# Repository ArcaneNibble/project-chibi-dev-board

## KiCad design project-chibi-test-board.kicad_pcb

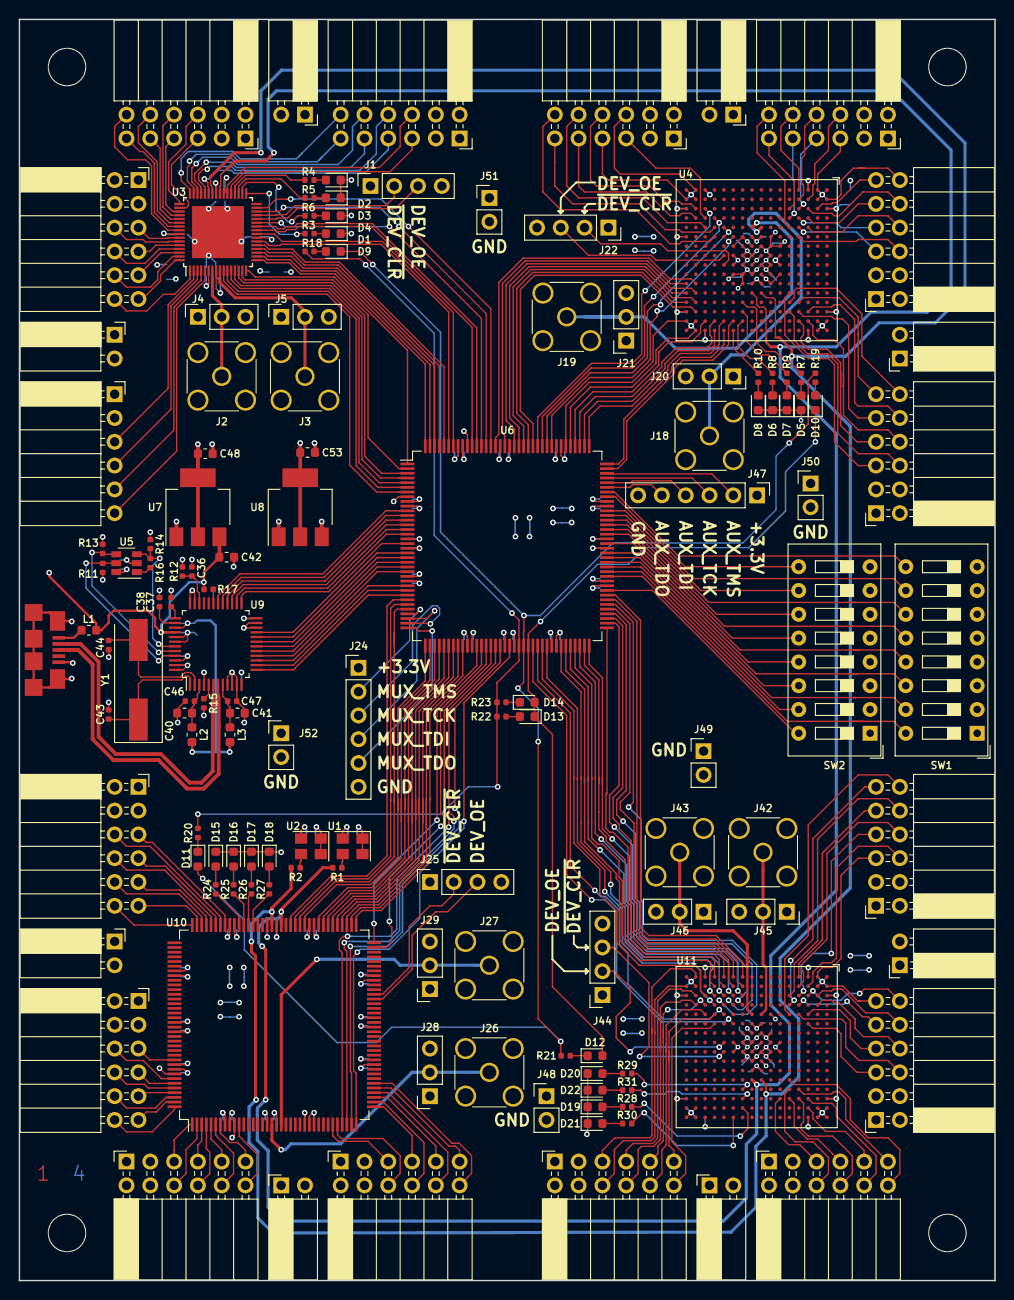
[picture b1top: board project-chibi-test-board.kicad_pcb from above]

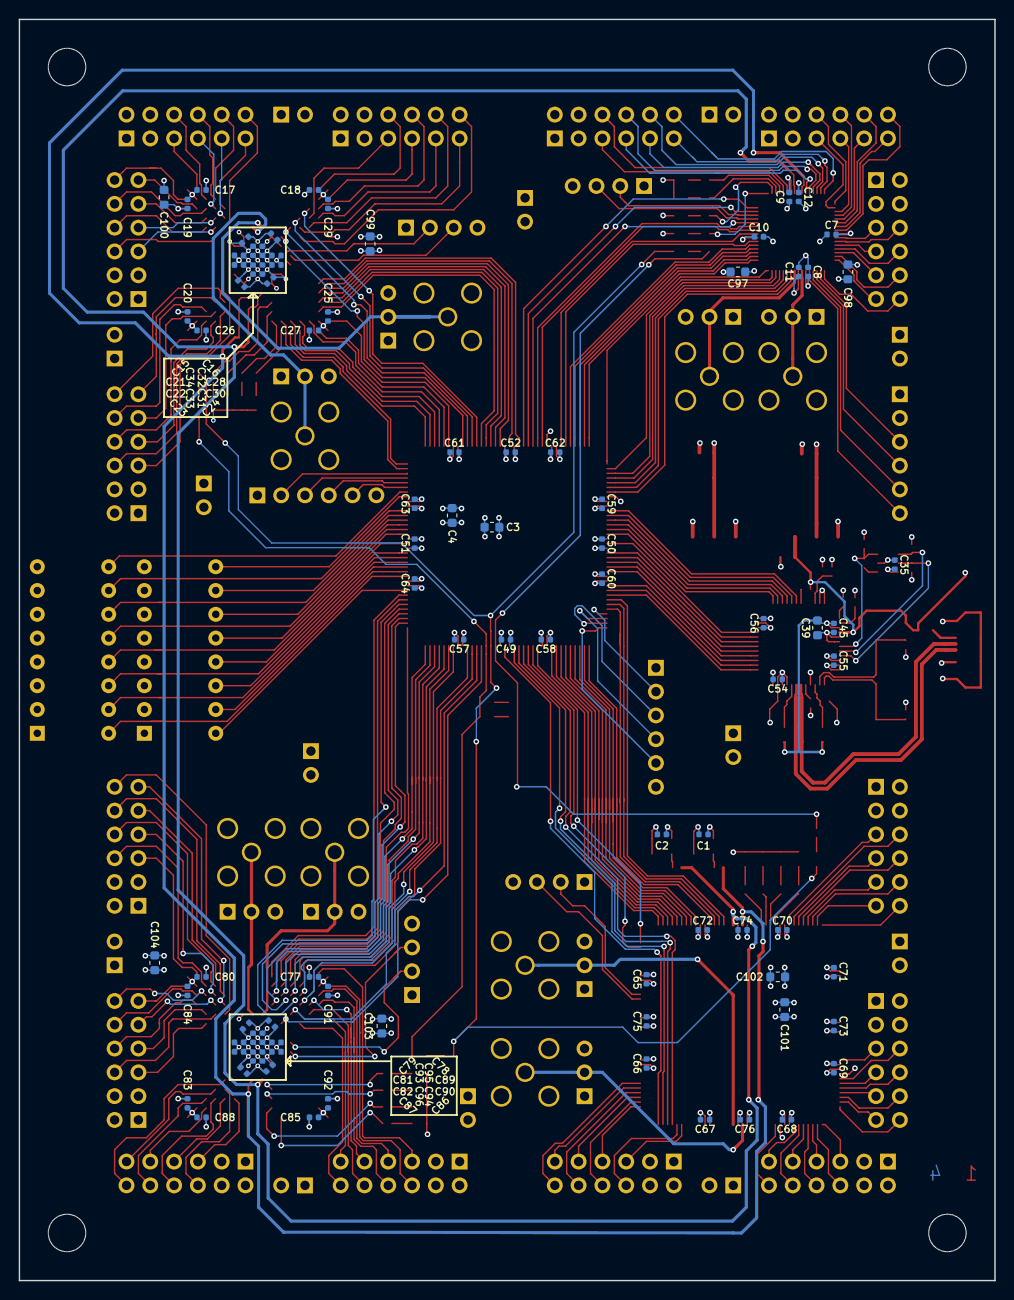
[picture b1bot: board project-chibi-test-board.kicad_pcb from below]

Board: 4 copper layers, 104.1 x 134.6 mm, 226 parts (88 on the bottom side), 321 nets.

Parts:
C1, C2, C7, C8, C9, C10, C11, C12, C15, C16, C17, C18, C19, C20, C21, C22, C23, C24, C25, C26, C27, C28, C29, C30, C31, C32, C33, C34, C35, C37, C38, C45, C46, C47, C49, C50, C51, C52, C54, C55, C56, C57, C58, C59, C60, C61, C62, C63, C64, C65, C66, C67, C68, C69, C70, C71, C72, C73, C74, C75, C76, C77, C78, C79, C80, C81, C82, C83, C84, C85, C86, C87, C88, C89, C90, C91, C92, C93, C94, C95, C96: 0.1 uF; C_0402_1005Metric
C3, C4, C39, C40, C41, C42, C48, C53, C97, C98, C99, C100, C101, C102, C103, C104: 4.7 uF; C_0603_1608Metric
C36: 10 nF; C_0402_1005Metric
C43, C44: 20 pF; C_0402_1005Metric
D1, D2, D3, D4, D5, D6, D7, D8, D15, D16, D17, D18, D19, D20, D21, D22: GREEN; LED_0603_1608Metric
D9, D10, D11, D12: RED; LED_0603_1608Metric
D13, D14: YELLOW; LED_0603_1608Metric
J1, J22, J25, J44: Conn_01x04; PinSocket_1x04_P2.54mm_Vertical
J2, J3, J18, J19, J26, J27, J42, J43: Conn_Coaxial; SMA_Amphenol_132134_Vertical
J4, J5, J20, J21, J28, J29, J45, J46: Conn_01x03; PinSocket_1x03_P2.54mm_Vertical
J6, J7, J8, J12, J13, J14, J15, J32, J33, J34, J35, J36, J37, J38, J39: Conn_02x06_Top_Bottom; PinSocket_2x06_P2.54mm_Horizontal
J9: Conn_01x06; PinSocket_1x06_P2.54mm_Horizontal
J10, J11, J16, J17, J30, J31, J40, J41: Conn_01x02; PinSocket_1x02_P2.54mm_Horizontal
J23: USB_B_Micro; USB-MICRO-AB
J24, J47: Conn_01x06; PinHeader_1x06_P2.54mm_Vertical
J48, J49, J50, J51, J52: Conn_01x02; PinHeader_1x02_P2.54mm_Vertical
L1, L2, L3: MPZ1608S601ATA00; L_0603_1608Metric
MK1, MK2, MK3, MK4: Mounting_Hole; MountingHole_4mm
R1, R2: 49.9; R_0402_1005Metric
R3, R4, R5, R6, R7, R8, R9, R10, R18, R19, R20, R21, R22, R23, R24, R25, R26, R27, R28, R29, R30, R31: 330; R_0402_1005Metric
R11, R12, R13, R14: 10k; R_0402_1005Metric
R15: 12k 1%; R_0402_1005Metric
R16: 2k; R_0402_1005Metric
R17: 39k; R_0402_1005Metric
SW1, SW2: SW_DIP_x08; SW_DIP_SPSTx08_Slide_9.78x22.5mm_W7.62mm_P2.54mm
U1: 40 MHz; Oscillator_SMD_Abracon_ASE-4Pin_3.2x2.5mm
U2: 2.048 MHz; Oscillator_SMD_Abracon_ASE-4Pin_3.2x2.5mm
U3: 5M40ZE64C5N; TQFP-64-1EP_7x7mm_P0.4mm_EP4.5x4.5mm
U4: 5M2210ZF256C5N; BGA-256_17.0x17.0mm_Layout16x16_P1.0mm_Ball0.5mm_Pad0.4mm_N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
U5: 93LC56BT-OT; SOT-23-6
U6, U10: 5M240ZT144C5N; TQFP-144_20x20mm_P0.5mm
U7: LM1117-3.3; SOT-223-3_TabPin2
U8: LM1117-1.8; SOT-223-3_TabPin2
U9: FT232H; LQFP-48_7x7mm_P0.5mm
U11: 5M1270ZF256C5N; BGA-256_17.0x17.0mm_Layout16x16_P1.0mm_Ball0.5mm_Pad0.4mm_N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
Y1: 12 MHz; Crystal_SMD_HC49-SD

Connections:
+1V8: C3.1, C11.1, C12.1, C31.1, C32.1, C33.1, C34.1, C49.1, C50.1, C51.1, C52.1, C53.1, C73.1, C74.1, C75.1, C76.1, C93.1, C94.1, C95.1, C96.1, C97.1, C99.1, C101.1, C103.1, U3.8, U3.41, U4.F10, U4.G11, U4.H8, U4.H10, U4.J7, U4.J9, U4.K6, U4.L7, U6.19, U6.56, U6.90, U6.126, U8.2, U10.19, U10.56, U10.90, U10.126, U11.H8, U11.H10, U11.J7, U11.J9
+3V3: C1.1, C2.1, C4.1, C7.1, C8.1, C9.1, C10.1, C15.1, C16.1, C17.1, C18.1, C19.1, C20.1, C21.1, C22.1, C23.1, C24.1, C25.1, C26.1, C27.1, C28.1, C29.1, C30.1, C35.1, C48.1, C54.1, C55.1, C56.1, C57.1, C58.1, C59.1, C60.1, C61.1, C62.1, C63.1, C64.1, C65.1, C66.1, C67.1, C68.1, C69.1, C70.1, C71.1, C72.1, C77.1, C78.1, C79.1, C80.1, C81.1, C82.1, C83.1, C84.1, C85.1, C86.1, C87.1, C88.1, C89.1, C90.1, C91.1, C92.1, C98.1, C100.1, C102.1, C104.1, J1.1, J6.1, J6.2, J7.1, J7.2, J8.1, J8.2, J9.1, J12.1, J12.2, J13.1, J13.2, J14.1, J14.2, J15.1, J15.2, J22.1, J24.1, J25.1, J32.1, J32.2, J33.1, J33.2, J34.1, J34.2, J35.1, J35.2, J36.1, J36.2, J37.1, J37.2, J38.1, J38.2, J39.1, J39.2, J44.1, J47.1, R11.1, R12.1, R13.1, R14.1, U1.1, U1.4, U2.1, U2.4, U3.6, U3.23, U3.39, U3.57, U4.A3, U4.A14, U4.C1, U4.C16, U4.F8, U4.F9, U4.H6, U4.H11, U4.J6, U4.J11, U4.L8, U4.L9, U4.P1, U4.P16, U4.T3, U4.T14, U5.6, U6.9, U6.25, U6.46, U6.64, U6.82, U6.100, U6.116, U6.136, U7.2, U8.3, U9.12, U9.24, U9.46, U10.9, U10.25, U10.46, U10.64, U10.82, U10.100, U10.116, U10.136, U11.A3, U11.A14, U11.C1, U11.C16, U11.F8, U11.F9, U11.H6, U11.H11, U11.J6, U11.J11, U11.L8, U11.L9, U11.P1, U11.P16, U11.T3, U11.T14
+5V: C42.1, J10.2, J11.2, J16.2, J17.2, J30.2, J31.2, J40.2, J41.2, L1.1, R17.1, U7.3, U9.40
/CLK_2.048MHZ: R2.1, U3.42, U4.H12, U10.91, U11.H12
/CLK_40MHZ: R1.1, U3.40, U4.J12, U10.89, U11.J12
/jtag-iface/ACBUS0: U6.18, U9.21
/jtag-iface/ACBUS1: U6.16, U9.25
/jtag-iface/ACBUS2: U6.15, U9.26
/jtag-iface/ACBUS3: U6.14, U9.27
/jtag-iface/ACBUS4: U6.13, U9.28
/jtag-iface/ACBUS5: U6.12, U9.29
/jtag-iface/ACBUS6: U6.11, U9.30
/jtag-iface/ADBUS0: U6.29, U9.13
/jtag-iface/ADBUS1: U6.28, U9.14
/jtag-iface/ADBUS2: U6.27, U9.15
/jtag-iface/ADBUS3: U6.24, U9.16
/jtag-iface/ADBUS4: U6.23, U9.17
/jtag-iface/ADBUS5: U6.22, U9.18
/jtag-iface/ADBUS6: U6.21, U9.19
/jtag-iface/ADBUS7: U6.20, U9.20
/jtag-iface/AUXJTAG_TCK: J47.3, U6.105
/jtag-iface/AUXJTAG_TDI: J47.4, U6.104
/jtag-iface/AUXJTAG_TDO: J47.5, U6.103
/jtag-iface/AUXJTAG_TMS: J47.2, U6.106
/jtag-iface/FTDI_VCCD: C39.1, C45.1, L2.2, L3.2, U9.39
/jtag-iface/FTDI_VPHY: C40.1, C46.1, L2.1, U9.3
/jtag-iface/FTDI_VPLL: C41.1, C47.1, L3.1, U9.8
/jtag-iface/MUX_TCK: J24.3, U6.35
/jtag-iface/MUX_TDI: J24.4, U6.34
/jtag-iface/MUX_TDO: J24.5, U6.36
/jtag-iface/MUX_TMS: J24.2, U6.33
/jtag-iface/USB_N: J23.2, U9.6
/jtag-iface/USB_P: J23.3, U9.7
/tgt-4x6/ACBUS0: U3.25, U6.134
/tgt-4x6/ACBUS1: U3.24, U6.138
/tgt-4x6/ACBUS2: U3.22, U6.139
/tgt-4x6/ACBUS3: U3.27, U6.132
/tgt-4x6/ACBUS4: U3.26, U6.133
/tgt-4x6/ACBUS5: U3.31, U6.130
/tgt-4x6/ACBUS6: U3.30, U6.131
/tgt-4x6/ADBUS0: U3.10, U6.7
/tgt-4x6/ADBUS1: U3.11, U6.6
/tgt-4x6/ADBUS2: U3.12, U6.5
/tgt-4x6/ADBUS3: U3.13, U6.4
/tgt-4x6/ADBUS4: U3.21, U6.140
/tgt-4x6/ADBUS5: U3.20, U6.141
/tgt-4x6/ADBUS6: U3.19, U6.142
/tgt-4x6/ADBUS7: U3.18, U6.143
/tgt-4x6/CLKIN0: J2.1, J4.2, U3.7
/tgt-4x6/CLKIN1: J3.1, J5.2, U3.9
/tgt-4x6/DEV_OE: J1.3, U3.28
/tgt-4x6/EXPAND0_0: J6.12, U3.1
/tgt-4x6/EXPAND0_1: J6.10, U3.63
/tgt-4x6/EXPAND0_2: J6.8, U3.61
/tgt-4x6/EXPAND0_3: J6.6, U3.59
/tgt-4x6/EXPAND0_4: J6.11, U3.64
/tgt-4x6/EXPAND0_5: J6.9, U3.62
/tgt-4x6/EXPAND0_6: J6.7, U3.60
/tgt-4x6/EXPAND0_7: J6.5, U3.58
/tgt-4x6/EXPAND1_0: J7.12, U3.56
/tgt-4x6/EXPAND1_1: J7.10, U3.54
/tgt-4x6/EXPAND1_2: J7.8, U3.52
/tgt-4x6/EXPAND1_3: J7.6, U3.49
/tgt-4x6/EXPAND1_4: J7.11, U3.55
/tgt-4x6/EXPAND1_5: J7.9, U3.53
/tgt-4x6/EXPAND1_6: J7.7, U3.51
/tgt-4x6/EXPAND1_7: J7.5, U3.50
/tgt-4x6/EXPAND2_0: J8.12, U3.48
/tgt-4x6/EXPAND2_1: J8.10, U3.46
/tgt-4x6/EXPAND2_2: J8.8, U3.44
/tgt-4x6/EXPAND2_3: J8.6, U3.38
/tgt-4x6/EXPAND2_4: J8.11, U3.47
/tgt-4x6/EXPAND2_5: J8.9, U3.45
/tgt-4x6/EXPAND2_6: J8.7, U3.43
/tgt-4x6/EXPAND2_7: J8.5, U3.37
/tgt-4x6/EXPAND3_0: J9.6, U3.5
/tgt-4x6/EXPAND3_1: J9.5, U3.4
/tgt-4x6/EXPAND3_2: J9.4, U3.3
/tgt-4x6/EXPAND3_3: J9.3, U3.2
/tgt-4x6/JTAG_TCK: U3.16, U6.1
/tgt-4x6/JTAG_TDI: U3.15, U6.2
/tgt-4x6/JTAG_TDO: U3.17, U6.144
/tgt-4x6/JTAG_TMS: U3.14, U6.3
/tgt-4x6/~DEV_CLR: J1.2, U3.29
/tgt-7x12/ACBUS0: U6.42, U10.77
/tgt-7x12/ACBUS1: U6.43, U10.76
/tgt-7x12/ACBUS2: U6.44, U10.75
/tgt-7x12/ACBUS3: U6.45, U10.74
/tgt-7x12/ACBUS4: U6.48, U10.73
/tgt-7x12/ACBUS5: U6.49, U10.72
/tgt-7x12/ACBUS6: U6.50, U10.71
/tgt-7x12/ADBUS0: U6.30, U10.87
/tgt-7x12/ADBUS1: U6.31, U10.86
/tgt-7x12/ADBUS2: U6.32, U10.85
/tgt-7x12/ADBUS3: U6.37, U10.84
/tgt-7x12/ADBUS4: U6.38, U10.81
/tgt-7x12/ADBUS5: U6.39, U10.80
/tgt-7x12/ADBUS6: U6.40, U10.79
/tgt-7x12/ADBUS7: U6.41, U10.78
/tgt-7x12/CLKIN0: J26.1, J28.2, U10.18
/tgt-7x12/CLKIN1: J27.1, J29.2, U10.20
/tgt-7x12/DEV_OE: J25.3, U10.60
/tgt-7x12/EXPAND0_0: J32.12, U10.11
/tgt-7x12/EXPAND0_1: J32.10, U10.6
/tgt-7x12/EXPAND0_2: J32.8, U10.4
/tgt-7x12/EXPAND0_3: J32.6, U10.2
/tgt-7x12/EXPAND0_4: J32.11, U10.7
/tgt-7x12/EXPAND0_5: J32.9, U10.5
/tgt-7x12/EXPAND0_6: J32.7, U10.3
/tgt-7x12/EXPAND0_7: J32.5, U10.1
/tgt-7x12/EXPAND1_0: J33.12, U10.42
/tgt-7x12/EXPAND1_1: J33.10, U10.40
/tgt-7x12/EXPAND1_2: J33.8, U10.38
/tgt-7x12/EXPAND1_3: J33.6, U10.32
/tgt-7x12/EXPAND1_4: J33.11, U10.41
/tgt-7x12/EXPAND1_5: J33.9, U10.39
/tgt-7x12/EXPAND1_6: J33.7, U10.37
/tgt-7x12/EXPAND1_7: J33.5, U10.31
/tgt-7x12/EXPAND2_0: J34.12, U10.108
/tgt-7x12/EXPAND2_1: J34.10, U10.106
/tgt-7x12/EXPAND2_2: J34.8, U10.104
/tgt-7x12/EXPAND2_3: J34.6, U10.102
/tgt-7x12/EXPAND2_4: J34.11, U10.107
/tgt-7x12/EXPAND2_5: J34.9, U10.105
/tgt-7x12/EXPAND2_6: J34.7, U10.103
/tgt-7x12/EXPAND2_7: J34.5, U10.101
/tgt-7x12/EXPAND3_0: J35.12, U10.144
/tgt-7x12/EXPAND3_1: J35.10, U10.142
/tgt-7x12/EXPAND3_2: J35.8, U10.140
/tgt-7x12/EXPAND3_3: J35.6, U10.138
/tgt-7x12/EXPAND3_4: J35.11, U10.143
/tgt-7x12/EXPAND3_5: J35.9, U10.141
/tgt-7x12/EXPAND3_6: J35.7, U10.139
/tgt-7x12/EXPAND3_7: J35.5, U10.134
/tgt-7x12/JTAG_TCK: U6.53, U10.35
/tgt-7x12/JTAG_TDI: U6.52, U10.34
/tgt-7x12/JTAG_TDO: U6.55, U10.36
/tgt-7x12/JTAG_TMS: U6.51, U10.33
/tgt-7x12/~DEV_CLR: J25.2, U10.61
/tgt-10x16/ACBUS0: U6.72, U11.K3
/tgt-10x16/ACBUS1: U6.70, U11.L3
/tgt-10x16/ACBUS2: U6.68, U11.M3
/tgt-10x16/ACBUS3: U6.66, U11.N3
/tgt-10x16/ACBUS4: U6.74, U11.K4
/tgt-10x16/ACBUS5: U6.76, U11.L4
/tgt-10x16/ACBUS6: U6.78, U11.M4
/tgt-10x16/ADBUS0: U6.80, U11.K1
/tgt-10x16/ADBUS1: U6.79, U11.K2
/tgt-10x16/ADBUS2: U6.77, U11.L1
/tgt-10x16/ADBUS3: U6.75, U11.L2
/tgt-10x16/ADBUS4: U6.73, U11.M1
/tgt-10x16/ADBUS5: U6.71, U11.M2
/tgt-10x16/ADBUS6: U6.69, U11.N1
/tgt-10x16/ADBUS7: U6.67, U11.N2
/tgt-10x16/CLK0: J42.1, J45.2, U11.H5
/tgt-10x16/CLK1: J43.1, J46.2, U11.J5
/tgt-10x16/DEV_OE: J44.2, U11.M8
/tgt-10x16/EXPAND0_0: J36.12, U11.C3
/tgt-10x16/EXPAND0_1: J36.10, U11.B3
/tgt-10x16/EXPAND0_2: J36.8, U11.B4
/tgt-10x16/EXPAND0_3: J36.6, U11.D5
/tgt-10x16/EXPAND0_4: J36.11, U11.A2
/tgt-10x16/EXPAND0_5: J36.9, U11.D4
/tgt-10x16/EXPAND0_6: J36.7, U11.C5
/tgt-10x16/EXPAND0_7: J36.5, U11.C6
/tgt-10x16/EXPAND1_0: J37.12, U11.E5
/tgt-10x16/EXPAND1_1: J37.10, U11.E3
/tgt-10x16/EXPAND1_2: J37.8, U11.D2
/tgt-10x16/EXPAND1_3: J37.6, U11.C2
/tgt-10x16/EXPAND1_4: J37.11, U11.E4
/tgt-10x16/EXPAND1_5: J37.9, U11.D1
/tgt-10x16/EXPAND1_6: J37.7, U11.D3
/tgt-10x16/EXPAND1_7: J37.5, U11.B1
/tgt-10x16/EXPAND2_0: J38.12, U11.E12
/tgt-10x16/EXPAND2_1: J38.10, U11.C14
/tgt-10x16/EXPAND2_2: J38.8, U11.D14
/tgt-10x16/EXPAND2_3: J38.6, U11.E13
/tgt-10x16/EXPAND2_4: J38.11, U11.D13
/tgt-10x16/EXPAND2_5: J38.9, U11.C15
/tgt-10x16/EXPAND2_6: J38.7, U11.E14
/tgt-10x16/EXPAND2_7: J38.5, U11.F14
/tgt-10x16/EXPAND3_0: J39.12, U11.N6
/tgt-10x16/EXPAND3_1: J39.10, U11.P5
/tgt-10x16/EXPAND3_2: J39.8, U11.R4
/tgt-10x16/EXPAND3_3: J39.6, U11.T2
/tgt-10x16/EXPAND3_4: J39.11, U11.N5
/tgt-10x16/EXPAND3_5: J39.9, U11.P4
/tgt-10x16/EXPAND3_6: J39.7, U11.R3
/tgt-10x16/EXPAND3_7: J39.5, U11.R1
/tgt-10x16/JTAG_TCK: U6.62, U11.P3
/tgt-10x16/JTAG_TDI: U6.60, U11.L6
/tgt-10x16/JTAG_TDO: U6.61, U11.M5
/tgt-10x16/JTAG_TMS: U6.63, U11.N4
/tgt-10x16/~DEV_CLR: J44.3, U11.M9
/tgt-13x20/ACBUS0: U4.R14, U6.121
/tgt-13x20/ACBUS1: U4.T13, U6.122
/tgt-13x20/ACBUS2: U4.R13, U6.123
/tgt-13x20/ACBUS3: U4.T12, U6.124
/tgt-13x20/ACBUS4: U4.R12, U6.125
/tgt-13x20/ACBUS5: U4.T11, U6.127
/tgt-13x20/ACBUS6: U4.R11, U6.129
/tgt-13x20/ADBUS0: U4.L15, U6.107
/tgt-13x20/ADBUS1: U4.M16, U6.108
/tgt-13x20/ADBUS2: U4.M15, U6.109
/tgt-13x20/ADBUS3: U4.N16, U6.110
/tgt-13x20/ADBUS4: U4.N15, U6.111
/tgt-13x20/ADBUS5: U4.P15, U6.112
/tgt-13x20/ADBUS6: U4.T15, U6.114
/tgt-13x20/ADBUS7: U4.R16, U6.113
/tgt-13x20/CLK0: J18.1, J20.2, U4.H5
/tgt-13x20/CLK1: J19.1, J21.2, U4.J5
/tgt-13x20/DEV_OE: J22.3, U4.M8
/tgt-13x20/EXPAND0_0: J12.12, U4.E5
/tgt-13x20/EXPAND0_1: J12.10, U4.D1
/tgt-13x20/EXPAND0_2: J12.8, U4.D2
/tgt-13x20/EXPAND0_3: J12.6, U4.C2
/tgt-13x20/EXPAND0_4: J12.11, U4.E3
/tgt-13x20/EXPAND0_5: J12.9, U4.E4
/tgt-13x20/EXPAND0_6: J12.7, U4.D3
/tgt-13x20/EXPAND0_7: J12.5, U4.B1
/tgt-13x20/EXPAND1_0: J13.12, U4.A2
/tgt-13x20/EXPAND1_1: J13.10, U4.C3
/tgt-13x20/EXPAND1_2: J13.8, U4.C5
/tgt-13x20/EXPAND1_3: J13.6, U4.D6
/tgt-13x20/EXPAND1_4: J13.11, U4.B3
/tgt-13x20/EXPAND1_5: J13.9, U4.C4
/tgt-13x20/EXPAND1_6: J13.7, U4.D4
/tgt-13x20/EXPAND1_7: J13.5, U4.D5
/tgt-13x20/EXPAND2_0: J14.12, U4.E13
/tgt-13x20/EXPAND2_1: J14.10, U4.C14
/tgt-13x20/EXPAND2_2: J14.8, U4.C15
/tgt-13x20/EXPAND2_3: J14.6, U4.E14
/tgt-13x20/EXPAND2_4: J14.11, U4.D13
/tgt-13x20/EXPAND2_5: J14.9, U4.D14
/tgt-13x20/EXPAND2_6: J14.7, U4.D15
/tgt-13x20/EXPAND2_7: J14.5, U4.E12
/tgt-13x20/EXPAND3_0: J15.12, U4.N6
/tgt-13x20/EXPAND3_1: J15.10, U4.P5
/tgt-13x20/EXPAND3_2: J15.8, U4.R3
/tgt-13x20/EXPAND3_3: J15.6, U4.R1
/tgt-13x20/EXPAND3_4: J15.11, U4.N5
/tgt-13x20/EXPAND3_5: J15.9, U4.R4
/tgt-13x20/EXPAND3_6: J15.7, U4.T2
/tgt-13x20/EXPAND3_7: J15.5, U4.P4
/tgt-13x20/JTAG_TCK: U4.P3, U6.120
/tgt-13x20/JTAG_TDI: U4.L6, U6.117
/tgt-13x20/JTAG_TDO: U4.M5, U6.118
/tgt-13x20/JTAG_TMS: U4.N4, U6.119
/tgt-13x20/~DEV_CLR: J22.2, U4.M9
GND: C1.2, C2.2, C3.2, C4.2, C7.2, C8.2, C9.2, C10.2, C11.2, C12.2, C15.2, C16.2, C17.2, C18.2, C19.2, C20.2, C21.2, C22.2, C23.2, C24.2, C25.2, C26.2, C27.2, C28.2, C29.2, C30.2, C31.2, C32.2, C33.2, C34.2, C35.2, C36.2, C37.2, C38.2, C39.2, C40.2, C41.2, C42.2, C43.2, C44.1, C45.2, C46.2, C47.2, C48.2, C49.2, C50.2, C51.2, C52.2, C53.2, C54.2, C55.2, C56.2, C57.2, C58.2, C59.2, C60.2, C61.2, C62.2, C63.2, C64.2, C65.2, C66.2, C67.2, C68.2, C69.2, C70.2, C71.2, C72.2, C73.2, C74.2, C75.2, C76.2, C77.2, C78.2, C79.2, C80.2, C81.2, C82.2, C83.2, C84.2, C85.2, C86.2, C87.2, C88.2, C89.2, C90.2, C91.2, C92.2, C93.2, C94.2, C95.2, C96.2, C97.2, C98.2, C99.2, C100.2, C101.2, C102.2, C103.2, C104.2, D1.1, D2.1, D3.1, D4.1, D5.1, D6.1, D7.1, D8.1, D15.1, D16.1, D17.1, D18.1, D19.1, D20.1, D21.1, D22.1, J1.4, J2.2, J3.2, J4.1, J4.3, J5.1, J5.3, J6.3, J6.4, J7.3, J7.4, J8.3, J8.4, J9.2, J10.1, J11.1, J12.3, J12.4, J13.3, J13.4, J14.3, J14.4, J15.3, J15.4, J16.1, J17.1, J18.2, J19.2, J20.1, J20.3, J21.1, J21.3, J22.4, J23.5, J23.6, J24.6, J25.4, J26.2, J27.2, J28.1, J28.3, J29.1, J29.3, J30.1, J31.1, J32.3, J32.4, J33.3, J33.4, J34.3, J34.4, J35.3, J35.4, J36.3, J36.4, J37.3, J37.4, J38.3, J38.4, J39.3, J39.4, J40.1, J41.1, J42.2, J43.2, J44.4, J45.1, J45.3, J46.1, J46.3, J47.6, J48.1, J48.2, J49.1, J49.2, J50.1, J50.2, J51.1, J51.2, J52.1, J52.2, R15.2, SW1.1, SW1.2, SW1.3, SW1.4, SW1.5, SW1.6, SW1.7, SW1.8, SW2.1, SW2.2, SW2.3, SW2.4, SW2.5, SW2.6, SW2.7, SW2.8, U1.2, U2.2, U3.65, U4.A1, U4.A16, U4.B2, U4.B15, U4.F7, U4.G6, U4.G7, U4.G8, U4.G9, U4.G10, U4.H7, U4.H9, U4.J8, U4.J10, U4.K7, U4.K8, U4.K9, U4.K10, U4.K11, U4.L10, U4.R2, U4.R15, U4.T1, U4.T6, U4.T16, U5.2, U6.8, U6.10, U6.17, U6.26, U6.47, U6.54, U6.65, U6.83, U6.92, U6.99, U6.115, U6.128, U6.135, U6.137, U7.1, U8.1, U9.4, U9.9, U9.10, U9.11, U9.22, U9.23, U9.35, U9.36, U9.41, U9.42, U9.47, U9.48, U10.8, U10.10, U10.17, U10.26, U10.47, U10.54, U10.65, U10.83, U10.92, U10.99, U10.115, U10.128, U10.135, U10.137, U11.A1, U11.A16, U11.B2, U11.B15, U11.G5, U11.G7, U11.G8, U11.G9, U11.G10, U11.H7, U11.H9, U11.J8, U11.J10, U11.K7, U11.K8, U11.K9, U11.K10, U11.R2, U11.R15, U11.T1, U11.T16
unnamed: C36.1, R12.2, U9.34
unnamed: C37.1, U9.37
unnamed: C38.1, U9.38
unnamed: C43.1, U9.1, Y1.1
unnamed: C44.2, U9.2, Y1.2
unnamed: D1.2, R3.2
unnamed: D2.2, R4.2
unnamed: D3.2, R5.2
unnamed: D4.2, R6.2
unnamed: D5.2, R7.2
unnamed: D6.2, R8.2
unnamed: D7.2, R9.2
unnamed: D8.2, R10.2
unnamed: D9.2, R18.2
unnamed: D10.1, D12.2, D13.1, D14.2, U6.59
unnamed: D10.2, R19.2
unnamed: D11.1, R20.2
unnamed: D9.1, D11.2, R19.1, R21.1, U6.58
unnamed: D12.1, R21.2
unnamed: D13.2, R22.2
unnamed: D14.1, R23.2
unnamed: D15.2, R24.2
unnamed: D16.2, R25.2
unnamed: D17.2, R26.2
unnamed: D18.2, R27.2
unnamed: D19.2, R28.2
unnamed: D20.2, R29.2
unnamed: D21.2, R30.2
unnamed: D22.2, R31.2
unnamed: J23.1, L1.2
unnamed: R1.2, U1.3
unnamed: R2.2, U2.3
unnamed: R3.1, U3.33
unnamed: R4.1, U3.36
unnamed: R5.1, U3.35
unnamed: R6.1, U3.34
unnamed: R7.1, U4.K13
unnamed: R8.1, U4.K15
unnamed: R9.1, U4.K14
unnamed: R10.1, U4.L16
unnamed: R11.2, U5.5, U9.45
unnamed: R13.2, U5.4, U9.44
unnamed: R14.2, R16.1, U5.3, U9.43
unnamed: R15.1, U9.5
unnamed: R16.2, U5.1
unnamed: R17.2, U9.31
unnamed: R18.1, R20.1, R22.1, R23.1, U6.57
unnamed: R24.1, U10.98
unnamed: R25.1, U10.97
unnamed: R26.1, U10.96
unnamed: R27.1, U10.95
unnamed: R28.1, U11.K15
unnamed: R29.1, U11.K13
unnamed: R30.1, U11.L16
unnamed: R31.1, U11.K14
unnamed: SW1.9, U6.102
unnamed: SW1.10, U6.98
unnamed: SW1.11, U6.96
unnamed: SW1.12, U6.94
unnamed: SW1.13, U6.91
unnamed: SW1.14, U6.88
unnamed: SW1.15, U6.86
unnamed: SW1.16, U6.84
unnamed: SW2.9, U6.101
unnamed: SW2.10, U6.97
unnamed: SW2.11, U6.95
unnamed: SW2.12, U6.93
unnamed: SW2.13, U6.89
unnamed: SW2.14, U6.87
unnamed: SW2.15, U6.85
unnamed: SW2.16, U6.81

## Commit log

2018-07-04 all pins? for 7x12 die
2018-07-04 all pin numbers for 7x12 die
2018-07-04 done 7x12 die
2018-07-04 Adjust pin lengths
2018-07-04 fix 7x12 die jtag; begin work on 13x20 die
2018-07-04 13x20 pin numbers
2018-07-04 done 13x20 die
2018-07-04 10x16 pin numbers
2018-07-04 10x16 done
2018-07-04 Add sheets for every target
2018-07-04 Add jtag sheet; update metadata
2018-07-05 sketch of jtag interface
2018-07-05 sketch of each target
2018-07-05 sketch of LEDs/jtag
2018-07-05 PMODs in target 0
2018-07-05 all PMODs
2018-07-05 cleanups
2018-07-05 Many footprints assigned
2018-07-05 fp table
2018-07-05 Rotate PMODs to match kicad pin numbering
2018-07-05 assign many footprints
2018-07-05 fix broken symbols
2018-07-05 altera exposed pad
2018-07-05 all footprints assigned
2018-07-05 initial rough placement, too big physically
2018-07-05 more detailed placement
2018-07-05 misc
2018-07-06 first order approximation of planes
2018-07-06 clean up 40z pin ordering
2018-07-06 clean up 240z pin ordering
2018-07-06 clean up 1270z pin ordering
2018-07-06 clean up 2210z pin ordering
2018-07-06 rough reorganized middle chip layout
2018-07-06 remove mask from test pattern
2018-07-07 add gnd test points
2018-07-07 rough 50z routing
2018-07-07 rough 240z routing
2018-07-07 rough 1270z routing
2018-07-07 rough 2240z routing
2018-07-07 massive mux pin reswap
2018-07-08 work on qfp decoupling; one bga decoupling
2018-07-08 most routing done except leds; oscillators
2018-07-08 rough draft routing
2018-07-08 tweaks
2018-07-08 more tweaks
2018-07-08 front silk cleanup
2018-07-09 back silk cleanup
2018-07-09 fab layer cleanup
2018-07-09 labels
